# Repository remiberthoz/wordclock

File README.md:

# Wordclock

This repository contains source code and CAD files to build and program a
wordclock.

The wordclock is designed inside an IKEA frame (SANNAHED, 25x25 cm). Behind the
front glass panel, a black mask allows light through transparent letters which
are individually backlighted with colour LEDs.

The clock displayed in the picture above spells out the time in French
(*il est midi moins cinq: it is five to noon*), but
design can easily be adapted to other languages. In addition to time of the day,
extra text for special days (*i.e.* birthdays) is highlighted in other colours.
Letters can be used as pixels to display other forms of text. The picture below
displays today's date (*Lun 18 04*: Monday *Lundi* the 18th of April).

Lights are controlled via custom printed circuit boards, multichannel LED driver
integrated circuits, and an Arduino Nano Every board breaking out a AVR XMEGA
4809 microcontroller. Timekeeping is performed with an accurate Real Time Clock
(RTC, DS3231M). The clock is powered via 5V/4A on a barrel jack, and the RTC is
internaly powered from a coin cell to ensure timekeeping even when the clock is
unplugged.

The source code attempts to follow SOLID principles. It should be easy to update
by anyone willing to add features, modify the word layout, alter colours, add
animations, and so on. As examples, the git repository includes extra behaviours
for the clock:

- it can display time with numbers, using letters as pixels
  ([source](src/Behaviour/TimeInNumbers/)),
- similarly, it can display the date ([source](src/Behaviour/DateInNumbers/)),
- on startup, it shows a splash screen with a welcome message
  ([source](src/Behaviour/HelloMessage/)),
- to debug electrical connecticity and software mappings, LEDs can be controlled
to blink one at a time ([source](src/Behaviour/BlinkOneAtATime/)),

All behaviours can be loaded on the clock, one can then use physical buttons at
the back of the frame to switch between behaviours. These buttons also permit to
adjust the time and date.

# LICENSE

Unless otherwise mentioned, the source code is licensed by Rémi Berthoz under
the [MIT License](LICENSE.txt). Exceptions are:

- The OneButton library (in `src/Protocols/OneButtons`) used to control the
  hardware push-buttons, which is licensed by Matthias Hertel under a BSD style
  license (http://www.mathertel.de/License.aspx).

- The USB USART library (in `src/Protocols/USB_USART`), adapted from
  [ArduinoCore-megaavr](https://github.com/arduino/ArduinoCore-megaavr), which
  is licensed by Arduino SA. under the terms of the GNU Lesser General Public
  License.

- The `src/millis.cpp` file, adapted from
  [ArduinoCore-megaavr](https://github.com/arduino/ArduinoCore-megaavr), which
  is licensed by Arduino SA. under the terms of the GNU Lesser General Public
  License.

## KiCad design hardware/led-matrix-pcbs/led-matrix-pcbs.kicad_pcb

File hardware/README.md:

# KiCAD files for the project.

Contains both PCBs and mounting parts. PCBs ordered from JLCPCB, mounting parts
laser-cut ordered from Sculpteo.

* `led-matrix-pcbs` (pictures: [front with LEDs](../pictures/pcb-led-matrix-front-leds-soldered.jpg), [front without LEDs](../pictures/pcb-led-matrix-front.jpg), [back](../pictures/pcb-led-matrix-back.jpg)):
  * Main PCB, hosting the LEDs and the LED drivers. Each PCB contains 12 RGB
  LEDs in a 3x4 grid (36 LEDs total).
  * With 24 PCBs aranged in a 6x4 grid, one can get a 16x16 grid of RGB LEDs.
  * Each LED on a PCB is controlled via the onboard driver. The driver is
  controlled by a I2C interface, for which pinout is available on the PCB. The
  I2C address of the driver can be adjusted via the ADR pin (see driver
  datasheet).
* `led-matrix-bridge-pcbs` ([picture](../pictures/pcb-bridge-back.jpg)):
  * Connector PCB to join the `led-matrix-pcbs`. Each connector PCB can connect
  4 `led-matrix-pcbs` on a row.
  * This highly simplifies the I2C connections, the ADR configuration, and
  power delivery.
  * Connection between `led-matrix-pcbs` and `led-matrix-bridge-pcbs` is easy
  with pin headers.
  * With 6 PCBs, one can connect 6 rows of 4 `led-matrix-pcbs` to reach 256 RGD
  LEDs.
  * `led-matrix-bridge-pcbs` are easily connected to each other for power
  and for the SCL line of the I2C protocol. Pinout is available for the SDA line
  of the I2C protocol.
* `spacers-laser-cut`:
  * Design for laser-cut plates that hold the PCBs while letting the light of
  the LEDs through.

The main controller (that gives instructions to the LED drivers) is an Arduino
Nano Every. Timekeeping is performed by a DS3231M (breakout board from DFRobot).

## Bill of Materials

### Mounting parts

Laser-cut plates (Scultpeo):
  * 1x backplate-decor, MDF 3mm
  * 1x spacer-mount-leds, Ondulated cardboard 2.8mm
  * 1x spacer-mount-leds, Standard MDF 3mm
  * 2x spacer-nomount-leds-solderjoints, Grey compact cardboard 1mm

Screws (vis-express):
  * Screw M1.6X16 inox
  * Bolt M1.6 inox
  * Washer M2 nylon

### PCBs

PCBs (JLCPCB):
  * 24x led-matrix-pcbs, FR4 1.6mm

  | Matrix front (with LEDs) | Matrix front (without LEDs) | Matrix back |
  |:-----------------:|:--------------------:|:----:|
  |  |  |  |

  * 6x led-matrix-bridge-pcbs, FR4 1.6mm

  | Bridge, connects 4 `led-matrix-pcbs` together |
  |:------:|
  |  |

Electronic components (ordered from Mouser and hand-solder, or assembled by JLCPCB):

Count | Part description    | Manufacturer reference | Manufacturer | Odered from
------|---------------------|----------------|--------------|---------------------------
256 | RGB LED               | IN-P32TATRGB   | Inolux   | Mouser
24  | 36 channel LED driver | IS31FL3236A    | Integrated Silicon Solution | JLCPCB (C246443)
24  | 100 kOhm              | 0603WAF1003T5E | Uniroyal | JLCPCB (C25803)
24  | 3.83 kOhm             | 0603WAF3831T5E | Uniroyal | JLCPCB (C22982)
24  | 4.7 kOhm              | 0603WAJ0472T5E | Uniroyal | JLCPCB (C25999)
48  | 100 nF                | CC0603KRX7R9BB104 | Yageo | JLCPCB (C14663)
24  | 1 uF                  | CL10A105KB8NNNC | Samsung Electro-Mechanics | JLCPCB (C15849)

## Stack layers of PCB, mounting, components:

```
..........................................................  glass window
------------------          ------------------------------  paper with letter matrix cutout
~~~~~~\    /~~~~~~          ~~~~~~~~~~~~~~~~~~~~~~~~~~~~~~  ondulated cardboard (spacer-mount-leds)
       \__/                                                 16mm screw
XXXXXXXX||XXXXXXXX          XXXXXXXXXXXXXXXXXXXXXXXXXXXXXX  MDF (spacer-mount-leds)
XXXXXXXX||XXXXXXXX          XXXXXXXXXXXXXXXXXXXXXXXXXXXXXX
XXXXXXXX||XXXXXXXX \light / XXXXXXXXXXXXXXXXXXXXXXXXXXXXXX
::::::::||:::::     \cone/     ::::::::::    :::::::::::::  Compact cardboard  (spacer-nomount-leds-solderjoints)
::::::::||::::: __==========__ :::::::::: /\ :::::::::::::  Compact cardboard  (spacer-nomount-leds-solderjoints)
        ||    _/     LED      \_        _/  \_              Solder joints and LEDs
========||===============================|  |=============  PCB (led-matrix-pcbs)
========||===============================|  |=============
        ||                               |  |               Connector pin
        ||                               |  |
        ||                               |  |
========||===============================|  |=============  PCB (led-matrix-bridge-pcbs)
========||===============================|  |=============
      --||--                             \  /               Solder joints, screw washer
      BB||BB                              \/                Screw bold
        ||
```

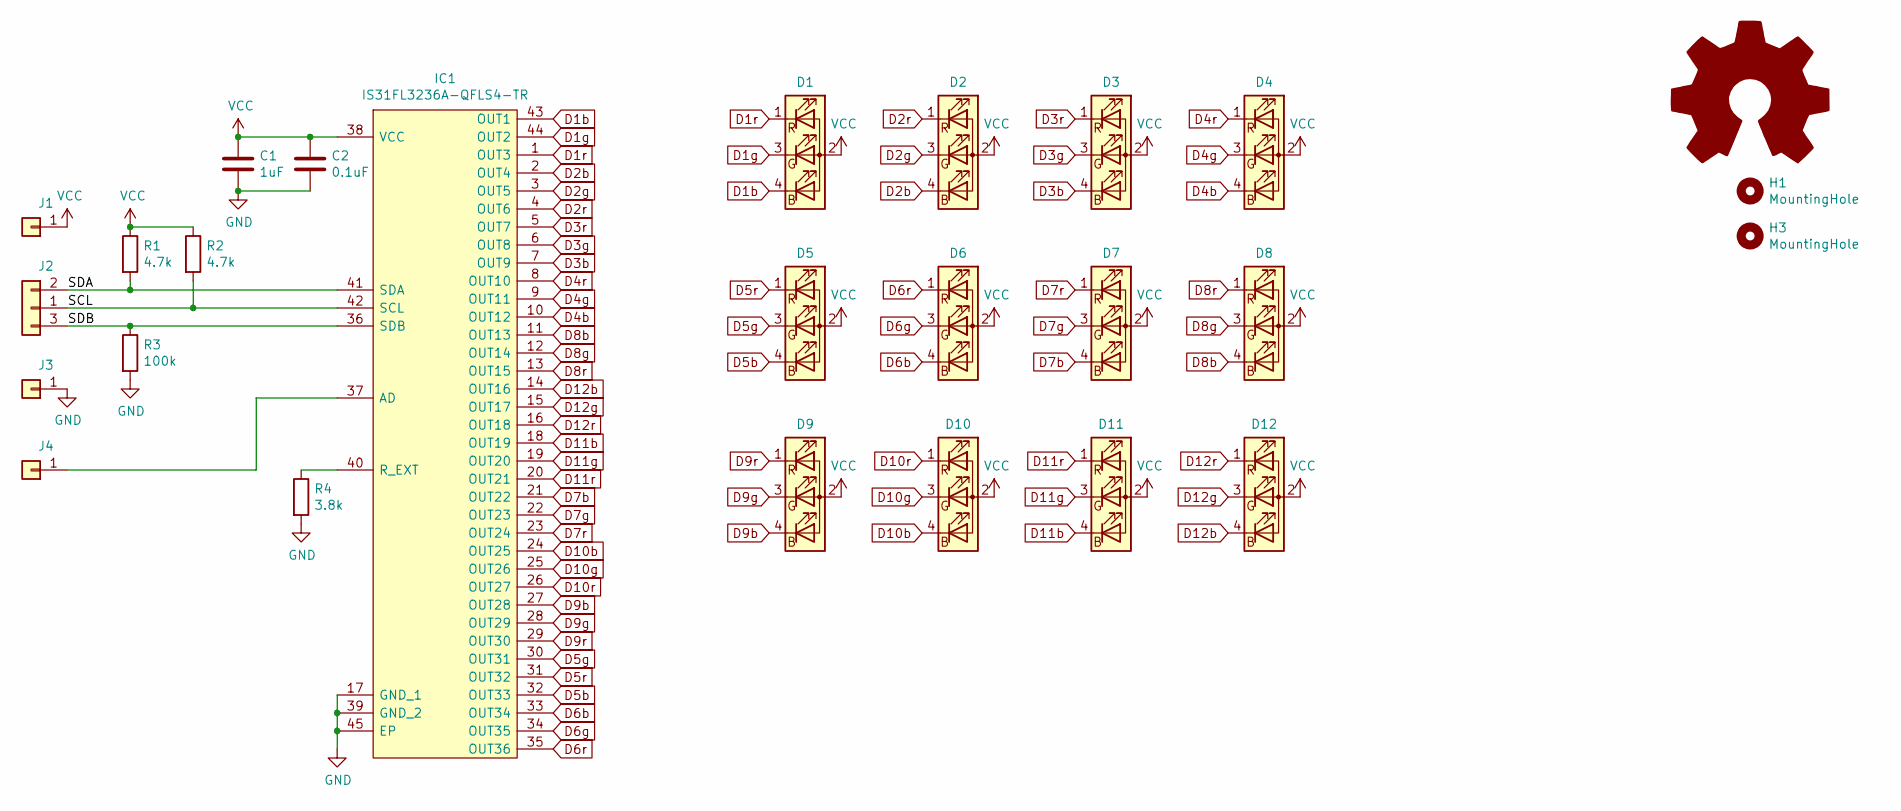
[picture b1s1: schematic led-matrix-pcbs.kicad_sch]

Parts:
C1: 1uF; C_0603_1608Metric; MouserNo 187-CL10B105KA8NNNC
C2: 0.1uF; C_0603_1608Metric; MouserNo 187-CL10B103KB8NNNC
D1, D2, D3, D4, D5, D6, D7, D8, D9, D10, D11, D12: LED_RAGB; INP32TATRGB; MouserNo 743-IN-P32TATRGB
H1, H3: MountingHole; #2-56; MouserNo na
IC1: IS31FL3236A-QFLS4-TR; IS31FL3236AQFLS4TR; Manufacturer_Part_Number IS31FL3236A-QFLS4-TR; MouserNo 870-IS31FL3236ATQLS4
J1, J3, J4: Conn_01x01; PinHeader_1x01_P2.54mm_Vertical; MouserNo na
J2: 01x03_312; PinSocket_1x03_P2.54mm_Vertical; MouserNo na
LOGO1: Logo_Open_Hardware_Large; OSHW-Logo2_7.3x6mm_SilkScreen; MouserNo na
R1, R2: 4.7k; R_0603_1608Metric; MouserNo 755-ESR03EZPJ472
R3: 100k; R_0603_1608Metric; MouserNo 755-ESR03EZPJ104
R4: 3.8k; R_0603_1608Metric; MouserNo 755-ESR03EZPJ392

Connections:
/SCL: IC1.42 (SCL), J2.1, R2.2
/SDA: IC1.41 (SDA), J2.2, R1.2
/SDB: IC1.36 (SDB), J2.3, R3.1
D1b: D1.4 (BK), IC1.43 (OUT1)
D1g: D1.3 (GK), IC1.44 (OUT2)
D1r: D1.1 (RK), IC1.1 (OUT3)
D2b: D2.4 (BK), IC1.2 (OUT4)
D2g: D2.3 (GK), IC1.3 (OUT5)
D2r: D2.1 (RK), IC1.4 (OUT6)
D3b: D3.4 (BK), IC1.7 (OUT9)
D3g: D3.3 (GK), IC1.6 (OUT8)
D3r: D3.1 (RK), IC1.5 (OUT7)
D4b: D4.4 (BK), IC1.10 (OUT12)
D4g: D4.3 (GK), IC1.9 (OUT11)
D4r: D4.1 (RK), IC1.8 (OUT10)
D5b: D5.4 (BK), IC1.32 (OUT33)
D5g: D5.3 (GK), IC1.30 (OUT31)
D5r: D5.1 (RK), IC1.31 (OUT32)
D6b: D6.4 (BK), IC1.33 (OUT34)
D6g: D6.3 (GK), IC1.34 (OUT35)
D6r: D6.1 (RK), IC1.35 (OUT36)
D7b: D7.4 (BK), IC1.21 (OUT22)
D7g: D7.3 (GK), IC1.22 (OUT23)
D7r: D7.1 (RK), IC1.23 (OUT24)
D8b: D8.4 (BK), IC1.11 (OUT13)
D8g: D8.3 (GK), IC1.12 (OUT14)
D8r: D8.1 (RK), IC1.13 (OUT15)
D9b: D9.4 (BK), IC1.27 (OUT28)
D9g: D9.3 (GK), IC1.28 (OUT29)
D9r: D9.1 (RK), IC1.29 (OUT30)
D10b: D10.4 (BK), IC1.24 (OUT25)
D10g: D10.3 (GK), IC1.25 (OUT26)
D10r: D10.1 (RK), IC1.26 (OUT27)
D11b: D11.4 (BK), IC1.18 (OUT19)
D11g: D11.3 (GK), IC1.19 (OUT20)
D11r: D11.1 (RK), IC1.20 (OUT21)
D12b: D12.4 (BK), IC1.14 (OUT16)
D12g: D12.3 (GK), IC1.15 (OUT17)
D12r: D12.1 (RK), IC1.16 (OUT18)
GND: C1.2, C2.2, IC1.17 (GND_1), IC1.39 (GND_2), IC1.45 (EP), J3.1, R3.2, R4.2
unnamed: IC1.37 (AD), J4.1
unnamed: IC1.40 (R_EXT), R4.1
VCC: C1.1, C2.1, D1.2 (A), D2.2 (A), D3.2 (A), D4.2 (A), D5.2 (A), D6.2 (A), D7.2 (A), D8.2 (A), D9.2 (A), D10.2 (A), D11.2 (A), D12.2 (A), IC1.38 (VCC), J1.1, R1.1, R2.1

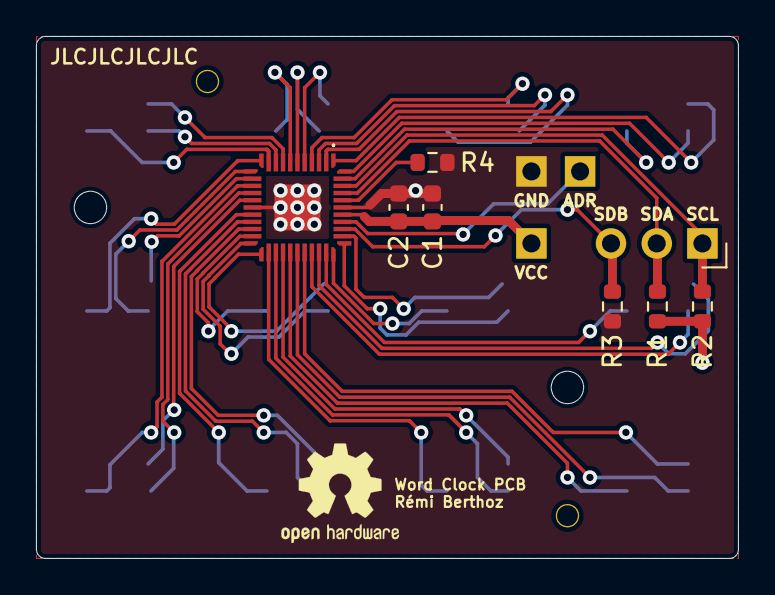
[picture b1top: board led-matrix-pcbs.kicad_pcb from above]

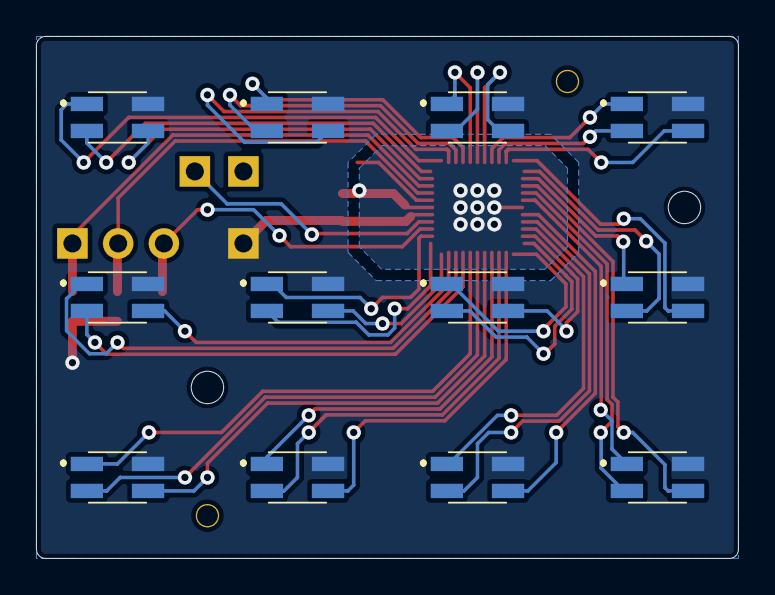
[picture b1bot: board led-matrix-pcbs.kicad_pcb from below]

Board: 2 copper layers, 39.0 x 29.0 mm, 26 parts (13 on the bottom side), 43 nets.

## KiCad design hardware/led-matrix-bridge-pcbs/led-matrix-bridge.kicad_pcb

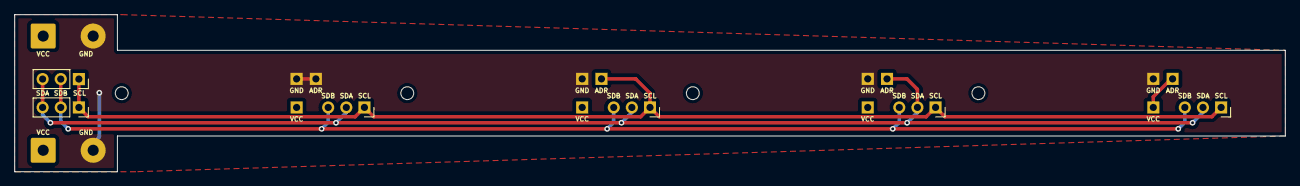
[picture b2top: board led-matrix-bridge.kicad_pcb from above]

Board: 2 copper layers, 178.0 x 22.0 mm, 24 parts (0 on the bottom side), 2 nets.

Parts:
H1, H2, H5, H7: MountingHole; #2-56
J1, J3, J4, J5, J7, J8, J9, J11, J12, J13, J15, J16: Conn_01x01; PinHeader_1x01_P2.54mm_Vertical
J2, J6, J10, J14, J18, J20: Conn_01x03; PinSocket_1x03_P2.54mm_Vertical
J17, J19: Conn_01x02; SolderWire-0.75sqmm_1x02_P7mm_D1.25mm_OD3.5mm

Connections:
GND: J3.1, J4.1, J8.1, J12.1, J16.1, J17.2, J19.2
VCC: J1.1, J5.1, J9.1, J13.1, J15.1, J17.1, J19.1

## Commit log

2022-05-15 Add hardware files
2022-05-15 Initial commit - working version of the clock
2022-05-15 Add LICENSE.txt file
2022-05-15 Add README with pictures
2022-05-28 Update README and pictures
2022-05-28 Update hardware README and pictures
